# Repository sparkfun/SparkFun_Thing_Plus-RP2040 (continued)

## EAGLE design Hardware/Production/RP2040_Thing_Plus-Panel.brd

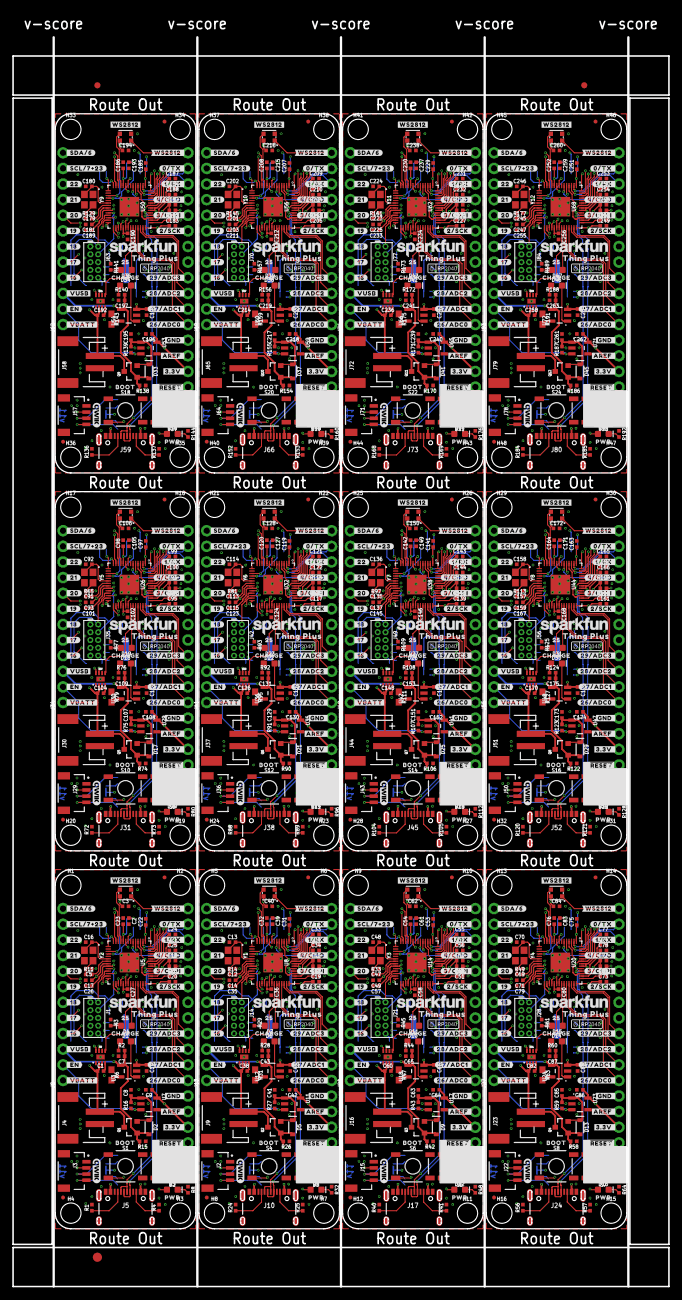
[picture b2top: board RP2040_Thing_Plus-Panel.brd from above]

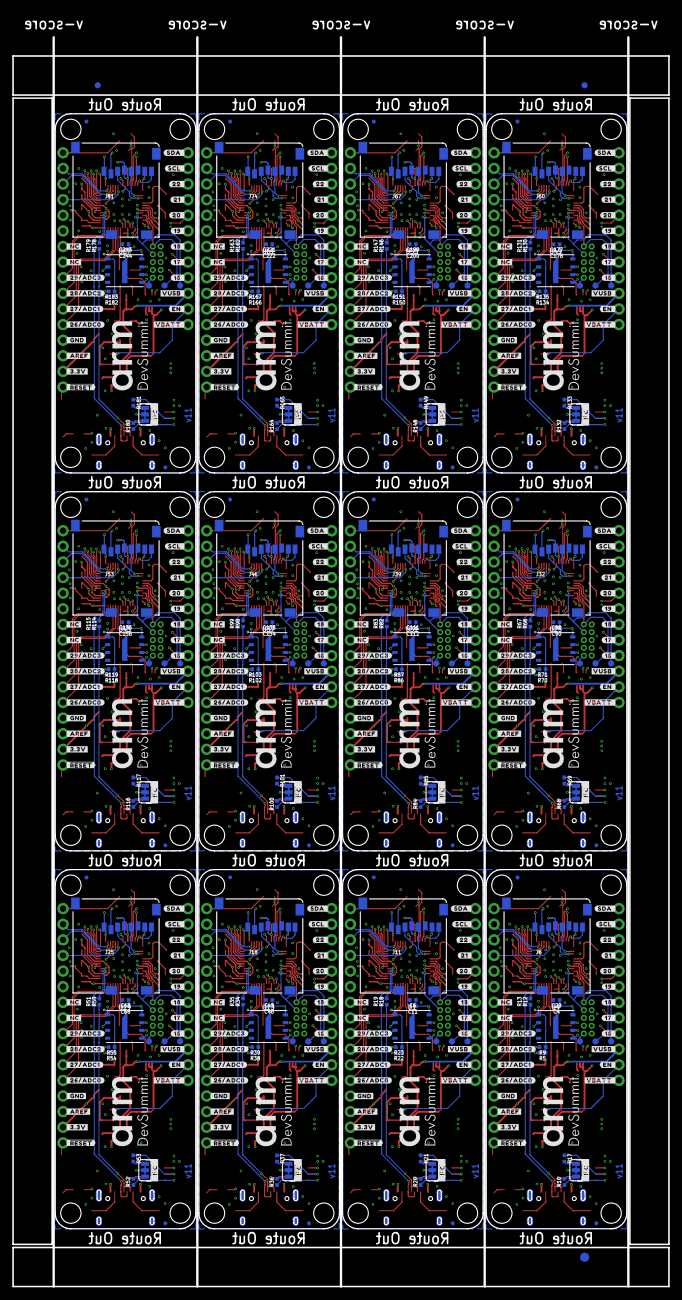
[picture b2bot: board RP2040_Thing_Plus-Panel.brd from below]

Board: 4 copper layers, 106.7 x 203.2 mm, 1566 parts (483 on the bottom side), 744 nets.

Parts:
C1, C2, C3, C6, C14, C15, C17, C18, C19, C20, C21, C22, C23, C24, C25, C29, C30, C31, C32, C33, C34, C38, C39, C40, C45, C49, C50, C51, C52, C53, C54, C55, C56, C60, C61, C62, C67, C71, C72, C73, C74, C75, C76, C77, C78, C82, C83, C84, C89, C93, C94, C95, C96, C97, C98, C99, C100, C104, C105, C106, C111, C115, C116, C117, C118, C119, C120, C121, C122, C126, C127, C128, C133, C137, C138, C139, C140, C141, C142, C143, C144, C148, C149, C150, C155, C159, C160, C161, C162, C163, C164, C165, C166, C170, C171, C172, C177, C181, C182, C183, C184, C185, C186, C187, C188, C192, C193, C194, C199, C203, C204, C205, C206, C207, C208, C209, C210, C214, C215, C216, C221, C225, C226, C227, C228, C229, C230, C231, C232, C236, C237, C238, C243, C247, C248, C249, C250, C251, C252, C253, C254, C258, C259, C260: 0.1uF; 0402-TIGHT
C4, C9, C11, C26, C27, C28, C35, C36, C37, C42, C46, C57, C58, C59, C64, C68, C79, C80, C81, C86, C90, C101, C102, C103, C108, C112, C123, C124, C125, C130, C134, C145, C146, C147, C152, C156, C167, C168, C169, C174, C178, C189, C190, C191, C196, C200, C211, C212, C213, C218, C222, C233, C234, C235, C240, C244, C255, C256, C257, C262: 2.2uF; 0402-TIGHT
C5, C12, C13, C16, C47, C48, C69, C70, C91, C92, C113, C114, C135, C136, C157, C158, C179, C180, C201, C202, C223, C224, C245, C246: 15pF; 0402-TIGHT
C7, C10, C43, C44, C65, C66, C87, C88, C109, C110, C131, C132, C153, C154, C175, C176, C197, C198, C219, C220, C241, C242, C263, C264: 4.7uF; 0402-TIGHT
C8, C41, C63, C85, C107, C129, C151, C173, C195, C217, C239, C261: 1.0uF; 0402-TIGHT
D1, D6, D10, D14, D18, D22, D26, D30, D34, D38, D42, D46: Yellow; LED-0603
D2, D5, D9, D13, D17, D21, D25, D29, D33, D37, D41, D45: 1A/23V/620mV; SOD-323
D3, D8, D12, D16, D20, D24, D28, D32, D36, D40, D44, D48: RED; LED-0603
D4, D7, D11, D15, D19, D23, D27, D31, D35, D39, D43, D47: BLUE; LED-0603
E$1, E$2, E$3, E$4: FIDUCIAL-1X2
E$5, E$6: FIDUCIAL-1.5X3
FD1, FD2, FD3, FD4, FD5, FD6, FD7, FD8, FD9, FD10, FD11, FD12, FD13, FD14, FD15, FD16, FD17, FD18, FD19, FD20, FD21, FD22, FD23, FD24, FD25, FD26, FD27, FD28, FD29, FD30, FD31, FD32, FD33, FD34, FD35, FD36, FD37, FD38, FD39, FD40, FD41, FD42, FD43, FD44, FD45, FD46, FD47, FD48: FIDUCIALUFIDUCIAL; FIDUCIAL-MICRO
H1, H2, H3, H4, H5, H6, H7, H8, H9, H10, H11, H12, H13, H14, H15, H16, H17, H18, H19, H20, H21, H22, H23, H24, H25, H26, H27, H28, H29, H30, H31, H32, H33, H34, H35, H36, H37, H38, H39, H40, H41, H42, H43, H44, H45, H46, H47, H48: STAND-OFF
J1, J14, J21, J28, J35, J42, J49, J56, J63, J70, J77, J84: SWD; 2X5-PTH-1.27MM
J2, J3, J15, J22, J29, J36, J43, J50, J57, J64, J71, J78: Qwiic; JST04_1MM_RA
J4, J9, J16, J23, J30, J37, J44, J51, J58, J65, J72, J79: JST-2-SMD
J5, J10, J17, J24, J31, J38, J45, J52, J59, J66, J73, J80: USB C; USB-C-16P-4LAYER-ISOLATED
J6, J11, J18, J25, J32, J39, J46, J53, J60, J67, J74, J81: microSD; MICRO-SD-SOCKET
J7, J12, J19, J26, J33, J40, J47, J54, J61, J68, J75, J82: 1X16_NO_SILK
J8, J13, J20, J27, J34, J41, J48, J55, J62, J69, J76, J83: 1X12_NO_SILK
JP1, JP2, JP3, JP4, JP5, JP6, JP7, JP8, JP9, JP10, JP11, JP12: JUMPER-SMT_3_2-NC_TRACE_SILK; SMT-JUMPER_3_2-NC_TRACE_SILK
Q1, Q2, Q3, Q4, Q5, Q6, Q7, Q8, Q9, Q10, Q11, Q12: 20V/4.2A/52mΩ/1.4W; SOT23-3
R1, R4, R24, R25, R40, R41, R56, R57, R72, R73, R88, R89, R104, R105, R120, R121, R136, R137, R152, R153, R168, R169, R184, R185: 5.1k; 0402-TIGHT
R2, R3, R5, R8, R11, R14, R22, R28, R29, R32, R33, R38, R44, R45, R48, R49, R54, R60, R61, R64, R65, R70, R76, R77, R80, R81, R86, R92, R93, R96, R97, R102, R108, R109, R112, R113, R118, R124, R125, R128, R129, R134, R140, R141, R144, R145, R150, R156, R157, R160, R161, R166, R172, R173, R176, R177, R182, R188, R189, R192: 1k; 0402-TIGHT
R6, R31, R47, R63, R79, R95, R111, R127, R143, R159, R175, R191: 2.0k; 0603
R7, R30, R46, R62, R78, R94, R110, R126, R142, R158, R174, R190: 200OHM-0402T-1/16W-1%; 0402-TIGHT
R9, R15, R16, R23, R26, R27, R39, R42, R43, R55, R58, R59, R71, R74, R75, R87, R90, R91, R103, R106, R107, R119, R122, R123, R135, R138, R139, R151, R154, R155, R167, R170, R171, R183, R186, R187: 10k; 0402-TIGHT
R10, R17, R20, R21, R36, R37, R52, R53, R68, R69, R84, R85, R100, R101, R116, R117, R132, R133, R148, R149, R164, R165, R180, R181: 2.2k; 0402-TIGHT
R12, R13, R18, R19, R34, R35, R50, R51, R66, R67, R82, R83, R98, R99, R114, R115, R130, R131, R146, R147, R162, R163, R178, R179: 27; 0402-TIGHT
S1, S2, S3, S4, S5, S6, S7, S8, S9, S10, S11, S12, S13, S14, S15, S16, S17, S18, S19, S20, S21, S22, S23, S24: MOMENTARY-SWITCH-SPST-SMD-5.2MM-TALL; TACTILE_SWITCH_SMD_5.2MM
TP1, TP2, TP3, TP4, TP5, TP6, TP7, TP8, TP9, TP10, TP11, TP12, TP13, TP14, TP15, TP16, TP17, TP18, TP19, TP20, TP21, TP22, TP23, TP24, TP25, TP26, TP27, TP28, TP29, TP30, TP31, TP32, TP33, TP34, TP35, TP36: PAD.03X.04
U1, U4, U13, U19, U25, U31, U37, U43, U49, U55, U61, U67: W25QXX128MBIT; WSON-8-6X5-SKINNY_CENTERPAD
U2, U9, U15, U21, U27, U33, U39, U45, U51, U57, U63, U69: MAX17048; DFN-8
U3, U12, U18, U24, U30, U36, U42, U48, U54, U60, U66, U72: MCP73831; SOT23-5
U5, U8, U14, U20, U26, U32, U38, U44, U50, U56, U62, U68: RP2040; QFN-56
U6, U10, U16, U22, U28, U34, U40, U46, U52, U58, U64, U70: WS2812-2020
U7, U11, U17, U23, U29, U35, U41, U47, U53, U59, U65, U71: 3.3V; SOT23-5
U$1, U$31, U$119, U$178, U$237, U$296, U$355, U$414, U$473, U$532, U$591, U$650: #_16#0
U$2, U$32, U$120, U$179, U$238, U$297, U$356, U$415, U$474, U$533, U$592, U$651: #_17#0
U$3, U$43, U$121, U$180, U$239, U$298, U$357, U$416, U$475, U$534, U$593, U$652: #_18#0
U$4, U$44, U$122, U$181, U$240, U$299, U$358, U$417, U$476, U$535, U$594, U$653: #_19#0
U$5, U$46, U$123, U$182, U$241, U$300, U$359, U$418, U$477, U$536, U$595, U$654: #_20#0
U$6, U$48, U$124, U$183, U$242, U$301, U$360, U$419, U$478, U$537, U$596, U$655: #_21#0
U$7, U$49, U$125, U$184, U$243, U$302, U$361, U$420, U$479, U$538, U$597, U$656: #_22#0
U$8, U$73, U$132, U$191, U$250, U$309, U$368, U$427, U$486, U$545, U$604, U$663: #_SCL#7#23#0
U$9, U$74, U$133, U$192, U$251, U$310, U$369, U$428, U$487, U$546, U$605, U$664: #_SDA#6#0
U$10, U$50, U$126, U$185, U$244, U$303, U$362, U$421, U$480, U$539, U$598, U$657: #WS2812_#0
U$11, U$51, U$127, U$186, U$245, U$304, U$363, U$422, U$481, U$540, U$599, U$658: #0#TX_#0
U$12, U$52, U$128, U$187, U$246, U$305, U$364, U$423, U$482, U$541, U$600, U$659: #1#RX_#0
U$13, U$53, U$129, U$188, U$247, U$306, U$365, U$424, U$483, U$542, U$601, U$660: #4#CIPO_#0
U$14, U$71, U$130, U$189, U$248, U$307, U$366, U$425, U$484, U$543, U$602, U$661: #3#COPI_#0
U$15, U$72, U$131, U$190, U$249, U$308, U$367, U$426, U$485, U$544, U$603, U$662: #2#SCK_#0
U$16, U$113, U$172, U$231, U$290, U$349, U$408, U$467, U$526, U$585, U$644, U$703: PWR0
U$17, U$114, U$173, U$232, U$291, U$350, U$409, U$468, U$527, U$586, U$645, U$704: #I�C#0
U$18, U$75, U$134, U$193, U$252, U$311, U$370, U$429, U$488, U$547, U$606, U$665: #29#ADC3_#0
U$19, U$76, U$135, U$194, U$253, U$312, U$371, U$430, U$489, U$548, U$607, U$666: #28#ADC2_#0
U$20, U$77, U$136, U$195, U$254, U$313, U$372, U$431, U$490, U$549, U$608, U$667: #27#ADC1_#0
U$21, U$78, U$137, U$196, U$255, U$314, U$373, U$432, U$491, U$550, U$609, U$668: #26#ADC0_#0
U$22, U$79, U$138, U$197, U$256, U$315, U$374, U$433, U$492, U$551, U$610, U$669: #_VUSB#0
U$23, U$80, U$139, U$198, U$257, U$316, U$375, U$434, U$493, U$552, U$611, U$670: #_EN#0
U$24, U$81, U$140, U$199, U$258, U$317, U$376, U$435, U$494, U$553, U$612, U$671: #_VBATT#0
U$25, U$82, U$141, U$200, U$259, U$318, U$377, U$436, U$495, U$554, U$613, U$672: #GND_#0
U$26, U$83, U$142, U$201, U$260, U$319, U$378, U$437, U$496, U$555, U$614, U$673: #AREF_#0
U$27, U$84, U$143, U$202, U$261, U$320, U$379, U$438, U$497, U$556, U$615, U$674: #3#3V_#0
U$28, U$85, U$144, U$203, U$262, U$321, U$380, U$439, U$498, U$557, U$616, U$675: ##RESET##0
U$29, U$117, U$176, U$235, U$294, U$353, U$412, U$471, U$530, U$589, U$648, U$707: RP2040_10
U$30, U$118, U$177, U$236, U$295, U$354, U$413, U$472, U$531, U$590, U$649, U$708: ARM1848_DEVSUMMIT_2021_LOGOS_ST3_STACKED#BLACK#JPG
U$33, U$101, U$160, U$219, U$278, U$337, U$396, U$455, U$514, U$573, U$632, U$691: #SCL_#0
U$34, U$102, U$161, U$220, U$279, U$338, U$397, U$456, U$515, U$574, U$633, U$692: #SDA_#0
U$35, U$103, U$162, U$221, U$280, U$339, U$398, U$457, U$516, U$575, U$634, U$693: #_#RESET##0
U$36, U$104, U$163, U$222, U$281, U$340, U$399, U$458, U$517, U$576, U$635, U$694: #_3#3V#0
U$37, U$105, U$164, U$223, U$282, U$341, U$400, U$459, U$518, U$577, U$636, U$695: #_AREF#0
U$38, U$106, U$165, U$224, U$283, U$342, U$401, U$460, U$519, U$578, U$637, U$696: #_GND#0
U$39, U$107, U$166, U$225, U$284, U$343, U$402, U$461, U$520, U$579, U$638, U$697: #_26#ADC0#0
U$40, U$108, U$167, U$226, U$285, U$344, U$403, U$462, U$521, U$580, U$639, U$698: #_27#ADC1#0
U$41, U$109, U$168, U$227, U$286, U$345, U$404, U$463, U$522, U$581, U$640, U$699: #_28#ADC2#0
U$42, U$110, U$169, U$228, U$287, U$346, U$405, U$464, U$523, U$582, U$641, U$700: #_29#ADC3#0
U$45, U$115, U$174, U$233, U$292, U$351, U$410, U$469, U$528, U$587, U$646, U$705: SFE_LOGO_NAME_.1
U$47, U$116, U$175, U$234, U$293, U$352, U$411, U$470, U$529, U$588, U$647, U$706: THING_PLUS_0
U$54, U$88, U$147, U$206, U$265, U$324, U$383, U$442, U$501, U$560, U$619, U$678: 250
U$55, U$89, U$148, U$207, U$266, U$325, U$384, U$443, U$502, U$561, U$620, U$679: CHARGE0
U$56, U$90, U$149, U$208, U$267, U$326, U$385, U$444, U$503, U$562, U$621, U$680: BOOT0
U$57, U$91, U$150, U$209, U$268, U$327, U$386, U$445, U$504, U$563, U$622, U$681: #22_#0
U$58, U$92, U$151, U$210, U$269, U$328, U$387, U$446, U$505, U$564, U$623, U$682: #21_#0
U$59, U$93, U$152, U$211, U$270, U$329, U$388, U$447, U$506, U$565, U$624, U$683: #20_#0
U$60, U$86, U$145, U$204, U$263, U$322, U$381, U$440, U$499, U$558, U$617, U$676: #WS2812#0
U$61, U$94, U$153, U$212, U$271, U$330, U$389, U$448, U$507, U$566, U$625, U$684: #19_#0
U$62, U$95, U$154, U$213, U$272, U$331, U$390, U$449, U$508, U$567, U$626, U$685: #18_#0
U$63, U$96, U$155, U$214, U$273, U$332, U$391, U$450, U$509, U$568, U$627, U$686: #17_#0
U$64, U$87, U$146, U$205, U$264, U$323, U$382, U$441, U$500, U$559, U$618, U$677: QWIIC_4MM
U$65, U$97, U$156, U$215, U$274, U$333, U$392, U$451, U$510, U$569, U$628, U$687: #16_#0
U$66, U$98, U$157, U$216, U$275, U$334, U$393, U$452, U$511, U$570, U$629, U$688: #VUSB_#0
U$67, U$99, U$158, U$217, U$276, U$335, U$394, U$453, U$512, U$571, U$630, U$689: #EN_#0
U$68, U$100, U$159, U$218, U$277, U$336, U$395, U$454, U$513, U$572, U$631, U$690: #VBATT_#0
U$69, U$70, U$111, U$112, U$170, U$171, U$229, U$230, U$288, U$289, U$347, U$348, U$406, U$407, U$465, U$466, U$524, U$525, U$583, U$584, U$642, U$643, U$701, U$702: #_NC#0
Y1, Y2, Y3, Y4, Y5, Y6, Y7, Y8, Y9, Y10, Y11, Y12: 12MHz; CRYSTAL-SMD-2X2.5MM

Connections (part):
1.1V: C24.1, C25.1, C26.1, U5.23, U5.45, U5.50
1.1V1: C33.1, C34.1, C35.1, U8.23, U8.45, U8.50
1.1V2: C55.1, C56.1, C57.1, U14.23, U14.45, U14.50
1.1V3: C77.1, C78.1, C79.1, U20.23, U20.45, U20.50
1.1V4: C99.1, C100.1, C101.1, U26.23, U26.45, U26.50
1.1V5: C121.1, C122.1, C123.1, U32.23, U32.45, U32.50
1.1V6: C143.1, C144.1, C145.1, U38.23, U38.45, U38.50
1.1V7: C165.1, C166.1, C167.1, U44.23, U44.45, U44.50
1.1V8: C187.1, C188.1, C189.1, U50.23, U50.45, U50.50
1.1V9: C209.1, C210.1, C211.1, U56.23, U56.45, U56.50
1.1V10: C231.1, C232.1, C233.1, U62.23, U62.45, U62.50
1.1V11: C253.1, C254.1, C255.1, U68.23, U68.45, U68.50
3.3V: C2.1, C3.1, C4.1, C9.1, C17.1, C18.1, C20.1, C21.1, C22.1, C23.1, C27.1, C29.1, D3.A, J1.1, J3.2, J6.VCC, J7.2, JP1.2, R7.2, R9.2, U4.8, U5.1, U5.10, U5.22, U5.33, U5.42, U5.44, U5.48, U5.49, U6.4, U7.5
3.3V1: C6.1, C11.1, C14.1, C15.1, C19.1, C30.1, C31.1, C32.1, C36.1, C39.1, C40.1, C42.1, D8.A, J2.2, J11.VCC, J12.2, J14.1, JP2.2, R23.2, R30.2, U1.8, U8.1, U8.10, U8.22, U8.33, U8.42, U8.44, U8.48, U8.49, U10.4, U11.5
3.3V2: C45.1, C46.1, C49.1, C50.1, C51.1, C52.1, C53.1, C54.1, C58.1, C61.1, C62.1, C64.1, D12.A, J15.2, J18.VCC, J19.2, J21.1, JP3.2, R39.2, R46.2, U13.8, U14.1, U14.10, U14.22, U14.33, U14.42, U14.44, U14.48, U14.49, U16.4, U17.5
3.3V3: C67.1, C68.1, C71.1, C72.1, C73.1, C74.1, C75.1, C76.1, C80.1, C83.1, C84.1, C86.1, D16.A, J22.2, J25.VCC, J26.2, J28.1, JP4.2, R55.2, R62.2, U19.8, U20.1, U20.10, U20.22, U20.33, U20.42, U20.44, U20.48, U20.49, U22.4, U23.5
3.3V4: C89.1, C90.1, C93.1, C94.1, C95.1, C96.1, C97.1, C98.1, C102.1, C105.1, C106.1, C108.1, D20.A, J29.2, J32.VCC, J33.2, J35.1, JP5.2, R71.2, R78.2, U25.8, U26.1, U26.10, U26.22, U26.33, U26.42, U26.44, U26.48, U26.49, U28.4, U29.5
3.3V5: C111.1, C112.1, C115.1, C116.1, C117.1, C118.1, C119.1, C120.1, C124.1, C127.1, C128.1, C130.1, D24.A, J36.2, J39.VCC, J40.2, J42.1, JP6.2, R87.2, R94.2, U31.8, U32.1, U32.10, U32.22, U32.33, U32.42, U32.44, U32.48, U32.49, U34.4, U35.5
3.3V6: C133.1, C134.1, C137.1, C138.1, C139.1, C140.1, C141.1, C142.1, C146.1, C149.1, C150.1, C152.1, D28.A, J43.2, J46.VCC, J47.2, J49.1, JP7.2, R103.2, R110.2, U37.8, U38.1, U38.10, U38.22, U38.33, U38.42, U38.44, U38.48, U38.49, U40.4, U41.5
3.3V7: C155.1, C156.1, C159.1, C160.1, C161.1, C162.1, C163.1, C164.1, C168.1, C171.1, C172.1, C174.1, D32.A, J50.2, J53.VCC, J54.2, J56.1, JP8.2, R119.2, R126.2, U43.8, U44.1, U44.10, U44.22, U44.33, U44.42, U44.44, U44.48, U44.49, U46.4, U47.5
3.3V8: C177.1, C178.1, C181.1, C182.1, C183.1, C184.1, C185.1, C186.1, C190.1, C193.1, C194.1, C196.1, D36.A, J57.2, J60.VCC, J61.2, J63.1, JP9.2, R135.2, R142.2, U49.8, U50.1, U50.10, U50.22, U50.33, U50.42, U50.44, U50.48, U50.49, U52.4, U53.5
3.3V9: C199.1, C200.1, C203.1, C204.1, C205.1, C206.1, C207.1, C208.1, C212.1, C215.1, C216.1, C218.1, D40.A, J64.2, J67.VCC, J68.2, J70.1, JP10.2, R151.2, R158.2, U55.8, U56.1, U56.10, U56.22, U56.33, U56.42, U56.44, U56.48, U56.49, U58.4, U59.5
3.3V10: C221.1, C222.1, C225.1, C226.1, C227.1, C228.1, C229.1, C230.1, C234.1, C237.1, C238.1, C240.1, D44.A, J71.2, J74.VCC, J75.2, J77.1, JP11.2, R167.2, R174.2, U61.8, U62.1, U62.10, U62.22, U62.33, U62.42, U62.44, U62.48, U62.49, U64.4, U65.5
3.3V11: C243.1, C244.1, C247.1, C248.1, C249.1, C250.1, C251.1, C252.1, C256.1, C259.1, C260.1, C262.1, D48.A, J78.2, J81.VCC, J82.2, J84.1, JP12.2, R183.2, R190.2, U67.8, U68.1, U68.10, U68.22, U68.33, U68.42, U68.44, U68.48, U68.49, U70.4, U71.5
!RESET!: J1.10, J7.1, S2.3, TP3.P$1, U5.26
!RESET!1: J12.1, J14.10, S3.3, TP6.P$1, U8.26
!RESET!2: J19.1, J21.10, S5.3, TP9.P$1, U14.26
!RESET!3: J26.1, J28.10, S7.3, TP12.P$1, U20.26
!RESET!4: J33.1, J35.10, S9.3, TP15.P$1, U26.26
!RESET!5: J40.1, J42.10, S11.3, TP18.P$1, U32.26
!RESET!6: J47.1, J49.10, S13.3, TP21.P$1, U38.26
!RESET!7: J54.1, J56.10, S15.3, TP24.P$1, U44.26
!RESET!8: J61.1, J63.10, S17.3, TP27.P$1, U50.26
!RESET!9: J68.1, J70.10, S19.3, TP30.P$1, U56.26
!RESET!10: J75.1, J77.10, S21.3, TP33.P$1, U62.26
!RESET!11: J82.1, J84.10, S23.3, TP36.P$1, U68.26
ADC0: J7.5, U5.38
ADC1: J7.6, U5.39
ADC2: J7.7, U5.40
ADC3: J7.8, U5.41
ADC4: J12.8, U8.41
ADC5: J12.5, U8.38
ADC6: J12.6, U8.39
ADC7: J12.7, U8.40
ADC8: J19.8, U14.41
ADC9: J19.5, U14.38
ADC10: J19.6, U14.39
ADC11: J19.7, U14.40
ADC12: J26.8, U20.41
ADC13: J26.5, U20.38
ADC14: J26.6, U20.39
ADC15: J26.7, U20.40
ADC16: J33.8, U26.41
ADC17: J33.5, U26.38
ADC18: J33.6, U26.39
ADC19: J33.7, U26.40
ADC20: J40.8, U32.41
ADC21: J40.5, U32.38
ADC22: J40.6, U32.39
ADC23: J40.7, U32.40
ADC24: J47.8, U38.41
ADC25: J47.5, U38.38
ADC26: J47.6, U38.39
ADC27: J47.7, U38.40
ADC28: J54.8, U44.41
ADC29: J54.5, U44.38
ADC30: J54.6, U44.39
ADC31: J54.7, U44.40
ADC32: J61.8, U50.41
ADC33: J61.5, U50.38
ADC34: J61.6, U50.39
ADC35: J61.7, U50.40
ADC36: J68.8, U56.41
ADC37: J68.5, U56.38
ADC38: J68.6, U56.39
ADC39: J68.7, U56.40
ADC40: J75.8, U62.41
ADC41: J75.5, U62.38
ADC42: J75.6, U62.39
ADC43: J75.7, U62.40
ADC44: J82.8, U68.41
ADC45: J82.5, U68.38
ADC46: J82.6, U68.39
ADC47: J82.7, U68.40
AVDD: C28.1, J7.3, R7.1, U5.43
AVDD1: C37.1, J12.3, R30.1, U8.43
AVDD2: C59.1, J19.3, R46.1, U14.43
AVDD3: C81.1, J26.3, R62.1, U20.43
AVDD4: C103.1, J33.3, R78.1, U26.43
AVDD5: C125.1, J40.3, R94.1, U32.43
AVDD6: C147.1, J47.3, R110.1, U38.43
AVDD7: C169.1, J54.3, R126.1, U44.43
AVDD8: C191.1, J61.3, R142.1, U50.43
AVDD9: C213.1, J68.3, R158.1, U56.43
AVDD10: C235.1, J75.3, R174.1, U62.43
AVDD11: C257.1, J82.3, R190.1, U68.43
BATT_ALERT: U2.5, U5.36
BATT_ALERT1: U8.36, U9.5
BATT_ALERT2: U14.36, U15.5
BATT_ALERT3: U20.36, U21.5
BATT_ALERT4: U26.36, U27.5
BATT_ALERT5: U32.36, U33.5
BATT_ALERT6: U38.36, U39.5
BATT_ALERT7: U44.36, U45.5
BATT_ALERT8: U50.36, U51.5
BATT_ALERT9: U56.36, U57.5
BATT_ALERT10: U62.36, U63.5
BATT_ALERT11: U68.36, U69.5
BOOT: R5.2, S1.3
BOOT1: R22.2, S4.3
BOOT2: R38.2, S6.3
BOOT3: R54.2, S8.3
BOOT4: R70.2, S10.3
BOOT5: R86.2, S12.3
BOOT6: R102.2, S14.3
BOOT7: R118.2, S16.3
BOOT8: R134.2, S18.3
BOOT9: R150.2, S20.3
BOOT10: R166.2, S22.3
BOOT11: R182.2, S24.3
EN: J8.2, R16.1, U7.3
EN1: J13.2, R27.1, U11.3
EN2: J20.2, R43.1, U17.3
EN3: J27.2, R59.1, U23.3
EN4: J34.2, R75.1, U29.3
EN5: J41.2, R91.1, U35.3
EN6: J48.2, R107.1, U41.3
EN7: J55.2, R123.1, U47.3
EN8: J62.2, R139.1, U53.3
EN9: J69.2, R155.1, U59.3
EN10: J76.2, R171.1, U65.3
EN11: J83.2, R187.1, U71.3
GND: C1.2, C2.2, C3.2, C4.2, C5.1, C7.2, C8.2, C9.2, C10.2, C16.1, C17.2, C18.2, C20.2, C21.2, C22.2, C23.2, C24.2, C25.2, C26.2, C27.2, C28.2, C29.2, J1.3, J1.5, J1.9, J3.1, J4.1, J5.GND, J5.GND2, J6.CD1, J6.GND, J6.GND1, J6.GND3, J7.4, R1.2, R3.1, R4.2, R6.1, R8.1, R15.1, S1.1, S2.1, U2.1, U2.4, U2.6, U2.9, U3.2, U4.4, U5.19, U5.EPAD, U6.2, U7.2
GND1: C6.2, C11.2, C12.1, C13.1, C14.2, C15.2, C19.2, C30.2, C31.2, C32.2, C33.2, C34.2, C35.2, C36.2, C37.2, C38.2, C39.2, C40.2, C41.2, C42.2, C43.2, C44.2, J2.1, J9.1, J10.GND, J10.GND2, J11.CD1, J11.GND, J11.GND1, J11.GND3, J12.4, J14.3, J14.5, J14.9, R24.2, R25.2, R26.1, R29.1, R31.1, R32.1, S3.1, S4.1, U1.4, U8.19, U8.EPAD, U9.1, U9.4, U9.6, U9.9, U10.2, U11.2, U12.2
GND2: C45.2, C46.2, C47.1, C48.1, C49.2, C50.2, C51.2, C52.2, C53.2, C54.2, C55.2, C56.2, C57.2, C58.2, C59.2, C60.2, C61.2, C62.2, C63.2, C64.2, C65.2, C66.2, J15.1, J16.1, J17.GND, J17.GND2, J18.CD1, J18.GND, J18.GND1, J18.GND3, J19.4, J21.3, J21.5, J21.9, R40.2, R41.2, R42.1, R45.1, R47.1, R48.1, S5.1, S6.1, U13.4, U14.19, U14.EPAD, U15.1, U15.4, U15.6, U15.9, U16.2, U17.2, U18.2
GND3: C67.2, C68.2, C69.1, C70.1, C71.2, C72.2, C73.2, C74.2, C75.2, C76.2, C77.2, C78.2, C79.2, C80.2, C81.2, C82.2, C83.2, C84.2, C85.2, C86.2, C87.2, C88.2, J22.1, J23.1, J24.GND, J24.GND2, J25.CD1, J25.GND, J25.GND1, J25.GND3, J26.4, J28.3, J28.5, J28.9, R56.2, R57.2, R58.1, R61.1, R63.1, R64.1, S7.1, S8.1, U19.4, U20.19, U20.EPAD, U21.1, U21.4, U21.6, U21.9, U22.2, U23.2, U24.2
GND4: C89.2, C90.2, C91.1, C92.1, C93.2, C94.2, C95.2, C96.2, C97.2, C98.2, C99.2, C100.2, C101.2, C102.2, C103.2, C104.2, C105.2, C106.2, C107.2, C108.2, C109.2, C110.2, J29.1, J30.1, J31.GND, J31.GND2, J32.CD1, J32.GND, J32.GND1, J32.GND3, J33.4, J35.3, J35.5, J35.9, R72.2, R73.2, R74.1, R77.1, R79.1, R80.1, S9.1, S10.1, U25.4, U26.19, U26.EPAD, U27.1, U27.4, U27.6, U27.9, U28.2, U29.2, U30.2
GND5: C111.2, C112.2, C113.1, C114.1, C115.2, C116.2, C117.2, C118.2, C119.2, C120.2, C121.2, C122.2, C123.2, C124.2, C125.2, C126.2, C127.2, C128.2, C129.2, C130.2, C131.2, C132.2, J36.1, J37.1, J38.GND, J38.GND2, J39.CD1, J39.GND, J39.GND1, J39.GND3, J40.4, J42.3, J42.5, J42.9, R88.2, R89.2, R90.1, R93.1, R95.1, R96.1, S11.1, S12.1, U31.4, U32.19, U32.EPAD, U33.1, U33.4, U33.6, U33.9, U34.2, U35.2, U36.2
GND6: C133.2, C134.2, C135.1, C136.1, C137.2, C138.2, C139.2, C140.2, C141.2, C142.2, C143.2, C144.2, C145.2, C146.2, C147.2, C148.2, C149.2, C150.2, C151.2, C152.2, C153.2, C154.2, J43.1, J44.1, J45.GND, J45.GND2, J46.CD1, J46.GND, J46.GND1, J46.GND3, J47.4, J49.3, J49.5, J49.9, R104.2, R105.2, R106.1, R109.1, R111.1, R112.1, S13.1, S14.1, U37.4, U38.19, U38.EPAD, U39.1, U39.4, U39.6, U39.9, U40.2, U41.2, U42.2
GND7: C155.2, C156.2, C157.1, C158.1, C159.2, C160.2, C161.2, C162.2, C163.2, C164.2, C165.2, C166.2, C167.2, C168.2, C169.2, C170.2, C171.2, C172.2, C173.2, C174.2, C175.2, C176.2, J50.1, J51.1, J52.GND, J52.GND2, J53.CD1, J53.GND, J53.GND1, J53.GND3, J54.4, J56.3, J56.5, J56.9, R120.2, R121.2, R122.1, R125.1, R127.1, R128.1, S15.1, S16.1, U43.4, U44.19, U44.EPAD, U45.1, U45.4, U45.6, U45.9, U46.2, U47.2, U48.2
GND8: C177.2, C178.2, C179.1, C180.1, C181.2, C182.2, C183.2, C184.2, C185.2, C186.2, C187.2, C188.2, C189.2, C190.2, C191.2, C192.2, C193.2, C194.2, C195.2, C196.2, C197.2, C198.2, J57.1, J58.1, J59.GND, J59.GND2, J60.CD1, J60.GND, J60.GND1, J60.GND3, J61.4, J63.3, J63.5, J63.9, R136.2, R137.2, R138.1, R141.1, R143.1, R144.1, S17.1, S18.1, U49.4, U50.19, U50.EPAD, U51.1, U51.4, U51.6, U51.9, U52.2, U53.2, U54.2
GND9: C199.2, C200.2, C201.1, C202.1, C203.2, C204.2, C205.2, C206.2, C207.2, C208.2, C209.2, C210.2, C211.2, C212.2, C213.2, C214.2, C215.2, C216.2, C217.2, C218.2, C219.2, C220.2, J64.1, J65.1, J66.GND, J66.GND2, J67.CD1, J67.GND, J67.GND1, J67.GND3, J68.4, J70.3, J70.5, J70.9, R152.2, R153.2, R154.1, R157.1, R159.1, R160.1, S19.1, S20.1, U55.4, U56.19, U56.EPAD, U57.1, U57.4, U57.6, U57.9, U58.2, U59.2, U60.2
GND10: C221.2, C222.2, C223.1, C224.1, C225.2, C226.2, C227.2, C228.2, C229.2, C230.2, C231.2, C232.2, C233.2, C234.2, C235.2, C236.2, C237.2, C238.2, C239.2, C240.2, C241.2, C242.2, J71.1, J72.1, J73.GND, J73.GND2, J74.CD1, J74.GND, J74.GND1, J74.GND3, J75.4, J77.3, J77.5, J77.9, R168.2, R169.2, R170.1, R173.1, R175.1, R176.1, S21.1, S22.1, U61.4, U62.19, U62.EPAD, U63.1, U63.4, U63.6, U63.9, U64.2, U65.2, U66.2
GND11: C243.2, C244.2, C245.1, C246.1, C247.2, C248.2, C249.2, C250.2, C251.2, C252.2, C253.2, C254.2, C255.2, C256.2, C257.2, C258.2, C259.2, C260.2, C261.2, C262.2, C263.2, C264.2, J78.1, J79.1, J80.GND, J80.GND2, J81.CD1, J81.GND, J81.GND1, J81.GND3, J82.4, J84.3, J84.5, J84.9, R184.2, R185.2, R186.1, R189.1, R191.1, R192.1, S23.1, S24.1, U67.4, U68.19, U68.EPAD, U69.1, U69.4, U69.6, U69.9, U70.2, U71.2, U72.2
GPIO1: J13.4, U8.27
GPIO2: J13.5, U8.28
GPIO3: J13.6, U8.29
GPIO4: J13.7, U8.30
GPIO5: J13.8, U8.31
GPIO6: J13.9, U8.32
GPIO7: J13.10, U8.34
GPIO8: J20.4, U14.27
GPIO9: J20.5, U14.28
GPIO10: J20.6, U14.29
GPIO11: J20.7, U14.30
GPIO12: J20.8, U14.31
GPIO13: J20.9, U14.32
GPIO14: J20.10, U14.34
GPIO15: J27.4, U20.27
GPIO16: J8.4, U5.27
GPIO17: J8.5, U5.28
GPIO18: J8.6, U5.29
GPIO19: J8.7, U5.30
GPIO20: J8.8, U5.31
GPIO21: J8.9, U5.32
GPIO22: J8.10, U5.34
GPIO23: J27.5, U20.28
GPIO24: J27.6, U20.29
GPIO25: J27.7, U20.30
GPIO26: J27.8, U20.31
GPIO27: J27.9, U20.32
GPIO28: J27.10, U20.34
GPIO29: J34.4, U26.27
GPIO30: J34.5, U26.28
GPIO31: J34.6, U26.29
GPIO32: J34.7, U26.30
GPIO33: J34.8, U26.31
GPIO34: J34.9, U26.32
GPIO35: J34.10, U26.34
GPIO36: J41.4, U32.27
GPIO37: J41.5, U32.28
GPIO38: J41.6, U32.29
GPIO39: J41.7, U32.30
GPIO40: J41.8, U32.31
GPIO41: J41.9, U32.32
GPIO42: J41.10, U32.34
GPIO43: J48.4, U38.27
GPIO44: J48.5, U38.28
GPIO45: J48.6, U38.29
GPIO46: J48.7, U38.30
GPIO47: J48.8, U38.31
GPIO48: J48.9, U38.32
GPIO49: J48.10, U38.34
GPIO50: J55.4, U44.27
GPIO51: J55.5, U44.28
GPIO52: J55.6, U44.29
GPIO53: J55.7, U44.30
GPIO54: J55.8, U44.31
GPIO55: J55.9, U44.32
GPIO56: J55.10, U44.34
GPIO57: J62.4, U50.27
GPIO58: J62.5, U50.28
GPIO59: J62.6, U50.29
GPIO60: J62.7, U50.30
GPIO61: J62.8, U50.31
GPIO62: J62.9, U50.32
GPIO63: J62.10, U50.34
GPIO64: J69.4, U56.27
GPIO65: J69.5, U56.28
GPIO66: J69.6, U56.29
GPIO67: J69.7, U56.30
GPIO68: J69.8, U56.31
GPIO69: J69.9, U56.32
GPIO70: J69.10, U56.34
GPIO71: J76.4, U62.27
GPIO72: J76.5, U62.28
GPIO73: J76.6, U62.29
GPIO74: J76.7, U62.30
GPIO75: J76.8, U62.31
GPIO76: J76.9, U62.32
GPIO77: J76.10, U62.34
GPIO78: J83.4, U68.27
GPIO79: J83.5, U68.28
GPIO80: J83.6, U68.29
GPIO81: J83.7, U68.30
GPIO82: J83.8, U68.31
GPIO83: J83.9, U68.32
GPIO84: J83.10, U68.34
I2C1_SCL/GPIO1: J2.4, J13.11, R20.1, U8.9, U8.35, U9.7
I2C1_SCL/GPIO2: J15.4, J20.11, R36.1, U14.9, U14.35, U15.7
I2C1_SCL/GPIO3: J22.4, J27.11, R52.1, U20.9, U20.35, U21.7
I2C1_SCL/GPIO4: J29.4, J34.11, R68.1, U26.9, U26.35, U27.7
I2C1_SCL/GPIO5: J36.4, J41.11, R84.1, U32.9, U32.35, U33.7
I2C1_SCL/GPIO6: J43.4, J48.11, R100.1, U38.9, U38.35, U39.7
I2C1_SCL/GPIO7: J50.4, J55.11, R116.1, U44.9, U44.35, U45.7
I2C1_SCL/GPIO8: J57.4, J62.11, R132.1, U50.9, U50.35, U51.7
I2C1_SCL/GPIO9: J64.4, J69.11, R148.1, U56.9, U56.35, U57.7
I2C1_SCL/GPIO10: J71.4, J76.11, R164.1, U62.9, U62.35, U63.7
I2C1_SCL/GPIO11: J78.4, J83.11, R180.1, U68.9, U68.35, U69.7
I2C1_SCL/GPIO23: J3.4, J8.11, R10.1, U2.7, U5.9, U5.35
I2C1_SDA: J3.3, J8.12, R17.1, U2.8, U5.8
I2C1_SDA1: J2.3, J13.12, R21.1, U8.8, U9.8
I2C1_SDA2: J15.3, J20.12, R37.1, U14.8, U15.8
I2C1_SDA3: J22.3, J27.12, R53.1, U20.8, U21.8
I2C1_SDA4: J29.3, J34.12, R69.1, U26.8, U27.8
I2C1_SDA5: J36.3, J41.12, R85.1, U32.8, U33.8
I2C1_SDA6: J43.3, J48.12, R101.1, U38.8, U39.8
I2C1_SDA7: J50.3, J55.12, R117.1, U44.8, U45.8
I2C1_SDA8: J57.3, J62.12, R133.1, U50.8, U51.8
I2C1_SDA9: J64.3, J69.12, R149.1, U56.8, U57.8
I2C1_SDA10: J71.3, J76.12, R165.1, U62.8, U63.8
I2C1_SDA11: J78.3, J83.12, R181.1, U68.8, U69.8
LED_BUILTIN: D4.A, U5.37
LED_BUILTIN1: D7.A, U8.37
LED_BUILTIN2: D11.A, U14.37
LED_BUILTIN3: D15.A, U20.37
LED_BUILTIN4: D19.A, U26.37
LED_BUILTIN5: D23.A, U32.37
LED_BUILTIN6: D27.A, U38.37
LED_BUILTIN7: D31.A, U44.37
LED_BUILTIN8: D35.A, U50.37
LED_BUILTIN9: D39.A, U56.37
LED_BUILTIN10: D43.A, U62.37
LED_BUILTIN11: D47.A, U68.37
unnamed: D4.C, R3.2
unnamed: JP1.3, R10.2
unnamed: JP1.1, R17.2
unnamed: R11.2, U5.21
unnamed: C16.2, U5.20, Y2.P3
unnamed: C5.2, R11.1, Y2.P1
unnamed: D3.C, R8.2
unnamed: D6.C, U12.1
unnamed: D1.C, U3.1
unnamed: R31.2, U12.5
unnamed: J5.A5, R1.1
unnamed: J5.B5, R4.1
unnamed: D6.A, R28.1
unnamed: R6.2, U3.5
unnamed: C8.1, D2.C, Q1.2, R16.2, U7.1
unnamed: D7.C, R29.2
unnamed: D1.A, R2.1
unnamed: JP2.3, R20.2
unnamed: JP2.1, R21.2
unnamed: R14.2, U8.21
unnamed: C13.2, U8.20, Y1.P3
unnamed: C12.2, R14.1, Y1.P1
unnamed: J10.A5, R24.1
unnamed: J10.B5, R25.1
unnamed: C41.1, D5.C, Q2.2, R27.2, U11.1
unnamed: D8.C, R32.2
unnamed: D10.C, U18.1
unnamed: R47.2, U18.5
unnamed: D10.A, R44.1
unnamed: D11.C, R45.2
unnamed: JP3.3, R36.2
unnamed: JP3.1, R37.2
unnamed: R33.2, U14.21
unnamed: C48.2, U14.20, Y3.P3
unnamed: C47.2, R33.1, Y3.P1
unnamed: J17.A5, R40.1
unnamed: J17.B5, R41.1
unnamed: C63.1, D9.C, Q3.2, R43.2, U17.1
unnamed: D12.C, R48.2
unnamed: D14.C, U24.1
unnamed: R63.2, U24.5
unnamed: D14.A, R60.1
unnamed: D15.C, R61.2
unnamed: JP4.3, R52.2
unnamed: JP4.1, R53.2
unnamed: R49.2, U20.21
unnamed: C70.2, U20.20, Y4.P3
unnamed: C69.2, R49.1, Y4.P1
unnamed: J24.A5, R56.1
unnamed: J24.B5, R57.1
unnamed: C85.1, D13.C, Q4.2, R59.2, U23.1
unnamed: D16.C, R64.2
unnamed: D18.C, U30.1
unnamed: R79.2, U30.5
unnamed: D18.A, R76.1
unnamed: D19.C, R77.2
unnamed: JP5.3, R68.2
unnamed: JP5.1, R69.2
unnamed: R65.2, U26.21
unnamed: C92.2, U26.20, Y5.P3
unnamed: C91.2, R65.1, Y5.P1
unnamed: J31.A5, R72.1
unnamed: J31.B5, R73.1
unnamed: C107.1, D17.C, Q5.2, R75.2, U29.1
unnamed: D20.C, R80.2
unnamed: D22.C, U36.1
unnamed: R95.2, U36.5
unnamed: D22.A, R92.1
unnamed: D23.C, R93.2
unnamed: JP6.3, R84.2
unnamed: JP6.1, R85.2
unnamed: R81.2, U32.21
unnamed: C114.2, U32.20, Y6.P3
unnamed: C113.2, R81.1, Y6.P1
unnamed: J38.A5, R88.1
unnamed: J38.B5, R89.1
unnamed: C129.1, D21.C, Q6.2, R91.2, U35.1
unnamed: D24.C, R96.2
unnamed: D26.C, U42.1
unnamed: R111.2, U42.5
unnamed: D26.A, R108.1
unnamed: D27.C, R109.2
unnamed: JP7.3, R100.2
unnamed: JP7.1, R101.2
unnamed: R97.2, U38.21
unnamed: C136.2, U38.20, Y7.P3
unnamed: C135.2, R97.1, Y7.P1
unnamed: J45.A5, R104.1
unnamed: J45.B5, R105.1
unnamed: C151.1, D25.C, Q7.2, R107.2, U41.1
unnamed: D28.C, R112.2
unnamed: D30.C, U48.1
unnamed: R127.2, U48.5
unnamed: D30.A, R124.1
unnamed: D31.C, R125.2
unnamed: JP8.3, R116.2
unnamed: JP8.1, R117.2
unnamed: R113.2, U44.21
unnamed: C158.2, U44.20, Y8.P3
unnamed: C157.2, R113.1, Y8.P1
unnamed: J52.A5, R120.1
unnamed: J52.B5, R121.1
unnamed: C173.1, D29.C, Q8.2, R123.2, U47.1
unnamed: D32.C, R128.2
unnamed: D34.C, U54.1
unnamed: R143.2, U54.5
unnamed: D34.A, R140.1
unnamed: D35.C, R141.2
unnamed: JP9.3, R132.2
unnamed: JP9.1, R133.2
unnamed: R129.2, U50.21
unnamed: C180.2, U50.20, Y9.P3
unnamed: C179.2, R129.1, Y9.P1
unnamed: J59.A5, R136.1
unnamed: J59.B5, R137.1
unnamed: C195.1, D33.C, Q9.2, R139.2, U53.1
unnamed: D36.C, R144.2
unnamed: D38.C, U60.1
unnamed: R159.2, U60.5
unnamed: D38.A, R156.1
unnamed: D39.C, R157.2
unnamed: JP10.3, R148.2
unnamed: JP10.1, R149.2
unnamed: R145.2, U56.21
unnamed: C202.2, U56.20, Y10.P3
unnamed: C201.2, R145.1, Y10.P1
unnamed: J66.A5, R152.1
unnamed: J66.B5, R153.1
unnamed: C217.1, D37.C, Q10.2, R155.2, U59.1
unnamed: D40.C, R160.2
unnamed: D42.C, U66.1
unnamed: R175.2, U66.5
unnamed: D42.A, R172.1
unnamed: D43.C, R173.2
unnamed: JP11.3, R164.2
unnamed: JP11.1, R165.2
unnamed: R161.2, U62.21
unnamed: C224.2, U62.20, Y11.P3
unnamed: C223.2, R161.1, Y11.P1
unnamed: J73.A5, R168.1
unnamed: J73.B5, R169.1
unnamed: C239.1, D41.C, Q11.2, R171.2, U65.1
unnamed: D44.C, R176.2
unnamed: D46.C, U72.1
unnamed: R191.2, U72.5
unnamed: D46.A, R188.1
unnamed: D47.C, R189.2
unnamed: JP12.3, R180.2
unnamed: JP12.1, R181.2
unnamed: R177.2, U68.21
unnamed: C246.2, U68.20, Y12.P3
unnamed: C245.2, R177.1, Y12.P1
unnamed: J80.A5, R184.1
unnamed: J80.B5, R185.1
unnamed: C261.1, D45.C, Q12.2, R187.2, U71.1
unnamed: D48.C, R192.2
QSPI-0: U4.5, U5.53
QSPI-1: U4.2, U5.55
QSPI-2: U4.3, U5.54
QSPI-3: U4.7, U5.51
QSPI-4: U1.5, U8.53
QSPI-5: U1.7, U8.51
QSPI-6: U1.2, U8.55
QSPI-7: U1.3, U8.54
QSPI-8: U13.5, U14.53
QSPI-9: U13.7, U14.51
QSPI-10: U13.2, U14.55
QSPI-11: U13.3, U14.54
QSPI-12: U19.5, U20.53
QSPI-13: U19.7, U20.51
QSPI-14: U19.2, U20.55
QSPI-15: U19.3, U20.54
QSPI-16: U25.5, U26.53
QSPI-17: U25.7, U26.51
QSPI-18: U25.2, U26.55
QSPI-19: U25.3, U26.54
QSPI-20: U31.5, U32.53
QSPI-21: U31.7, U32.51
QSPI-22: U31.2, U32.55
QSPI-23: U31.3, U32.54
QSPI-24: U37.5, U38.53
QSPI-25: U37.7, U38.51
QSPI-26: U37.2, U38.55
QSPI-27: U37.3, U38.54
QSPI-28: U43.5, U44.53
QSPI-29: U43.7, U44.51
QSPI-30: U43.2, U44.55
QSPI-31: U43.3, U44.54
QSPI-32: U49.5, U50.53
QSPI-33: U49.7, U50.51
QSPI-34: U49.2, U50.55
QSPI-35: U49.3, U50.54
QSPI-36: U55.5, U56.53
QSPI-37: U55.7, U56.51
QSPI-38: U55.2, U56.55
QSPI-39: U55.3, U56.54
QSPI-40: U61.5, U62.53
QSPI-41: U61.7, U62.51
QSPI-42: U61.2, U62.55
QSPI-43: U61.3, U62.54
QSPI-44: U67.5, U68.53
QSPI-45: U67.7, U68.51
QSPI-46: U67.2, U68.55
QSPI-47: U67.3, U68.54
QSPI-CLK: U4.6, U5.52
QSPI-CLK1: U1.6, U8.52
QSPI-CLK2: U13.6, U14.52
QSPI-CLK3: U19.6, U20.52
QSPI-CLK4: U25.6, U26.52
QSPI-CLK5: U31.6, U32.52
QSPI-CLK6: U37.6, U38.52
QSPI-CLK7: U43.6, U44.52
QSPI-CLK8: U49.6, U50.52
QSPI-CLK9: U55.6, U56.52
QSPI-CLK10: U61.6, U62.52
QSPI-CLK11: U67.6, U68.52
QSPI-CS: R5.1, R9.1, U4.1, U5.56
QSPI-CS1: R22.1, R23.1, U1.1, U8.56
QSPI-CS2: R38.1, R39.1, U13.1, U14.56
QSPI-CS3: R54.1, R55.1, U19.1, U20.56
QSPI-CS4: R70.1, R71.1, U25.1, U26.56
QSPI-CS5: R86.1, R87.1, U31.1, U32.56
QSPI-CS6: R102.1, R103.1, U37.1, U38.56
QSPI-CS7: R118.1, R119.1, U43.1, U44.56
QSPI-CS8: R134.1, R135.1, U49.1, U50.56
QSPI-CS9: R150.1, R151.1, U55.1, U56.56
QSPI-CS10: R166.1, R167.1, U61.1, U62.56
QSPI-CS11: R182.1, R183.1, U67.1, U68.56
SDIO_DAT1: J6.DAT1, U5.14
SDIO_DAT2: J6.DAT2, U5.13
SDIO_DAT3: J11.DAT1, U8.14
SDIO_DAT4: J11.DAT2, U8.13
SDIO_DAT5: J18.DAT1, U14.14
SDIO_DAT6: J18.DAT2, U14.13
SDIO_DAT7: J25.DAT1, U20.14
SDIO_DAT8: J25.DAT2, U20.13
SDIO_DAT9: J32.DAT1, U26.14
SDIO_DAT10: J32.DAT2, U26.13
SDIO_DAT11: J39.DAT1, U32.14
SDIO_DAT12: J39.DAT2, U32.13
SDIO_DAT13: J46.DAT1, U38.14
SDIO_DAT14: J46.DAT2, U38.13
SDIO_DAT15: J53.DAT1, U44.14
SDIO_DAT16: J53.DAT2, U44.13
SDIO_DAT17: J60.DAT1, U50.14
SDIO_DAT18: J60.DAT2, U50.13
SDIO_DAT19: J67.DAT1, U56.14
SDIO_DAT20: J67.DAT2, U56.13
SDIO_DAT21: J74.DAT1, U62.14
SDIO_DAT22: J74.DAT2, U62.13
SDIO_DAT23: J81.DAT1, U68.14
SDIO_DAT24: J81.DAT2, U68.13
SPI0_CIPO: J7.13, U5.6
SPI0_CIPO1: J12.13, U8.6
SPI0_CIPO2: J19.13, U14.6
SPI0_CIPO3: J26.13, U20.6
SPI0_CIPO4: J33.13, U26.6
SPI0_CIPO5: J40.13, U32.6
SPI0_CIPO6: J47.13, U38.6
SPI0_CIPO7: J54.13, U44.6
SPI0_CIPO8: J61.13, U50.6
SPI0_CIPO9: J68.13, U56.6
SPI0_CIPO10: J75.13, U62.6
SPI0_CIPO11: J82.13, U68.6
SPI0_COPI: J7.12, U5.5
SPI0_COPI1: J12.12, U8.5
SPI0_COPI2: J19.12, U14.5
SPI0_COPI3: J26.12, U20.5
SPI0_COPI4: J33.12, U26.5
SPI0_COPI5: J40.12, U32.5
SPI0_COPI6: J47.12, U38.5
SPI0_COPI7: J54.12, U44.5
SPI0_COPI8: J61.12, U50.5
SPI0_COPI9: J68.12, U56.5
SPI0_COPI10: J75.12, U62.5
SPI0_COPI11: J82.12, U68.5
SPI0_SCK: J7.11, U5.4
SPI0_SCK1: J12.11, U8.4
SPI0_SCK2: J19.11, U14.4
SPI0_SCK3: J26.11, U20.4
SPI0_SCK4: J33.11, U26.4
SPI0_SCK5: J40.11, U32.4
SPI0_SCK6: J47.11, U38.4
SPI0_SCK7: J54.11, U44.4
SPI0_SCK8: J61.11, U50.4
SPI0_SCK9: J68.11, U56.4
SPI0_SCK10: J75.11, U62.4
SPI0_SCK11: J82.11, U68.4
SPI_!CS1!/SDIO_DAT1: J11.CS/DAT3, U8.12
SPI_!CS1!/SDIO_DAT2: J18.CS/DAT3, U14.12
SPI_!CS1!/SDIO_DAT3: J6.CS/DAT3, U5.12
SPI_!CS1!/SDIO_DAT4: J25.CS/DAT3, U20.12
SPI_!CS1!/SDIO_DAT5: J32.CS/DAT3, U26.12
SPI_!CS1!/SDIO_DAT6: J39.CS/DAT3, U32.12
SPI_!CS1!/SDIO_DAT7: J46.CS/DAT3, U38.12
SPI_!CS1!/SDIO_DAT8: J53.CS/DAT3, U44.12
SPI_!CS1!/SDIO_DAT9: J60.CS/DAT3, U50.12
SPI_!CS1!/SDIO_DAT10: J67.CS/DAT3, U56.12
SPI_!CS1!/SDIO_DAT11: J74.CS/DAT3, U62.12
SPI_!CS1!/SDIO_DAT12: J81.CS/DAT3, U68.12
SPI_CIPO1/SDIO_DAT0: J6.DO/DAT0, U5.15
SPI_CIPO1/SDIO_DAT1: J11.DO/DAT0, U8.15
SPI_CIPO1/SDIO_DAT2: J18.DO/DAT0, U14.15
SPI_CIPO1/SDIO_DAT3: J25.DO/DAT0, U20.15
SPI_CIPO1/SDIO_DAT4: J32.DO/DAT0, U26.15
SPI_CIPO1/SDIO_DAT5: J39.DO/DAT0, U32.15
SPI_CIPO1/SDIO_DAT6: J46.DO/DAT0, U38.15
SPI_CIPO1/SDIO_DAT7: J53.DO/DAT0, U44.15
SPI_CIPO1/SDIO_DAT8: J60.DO/DAT0, U50.15
SPI_CIPO1/SDIO_DAT9: J67.DO/DAT0, U56.15
SPI_CIPO1/SDIO_DAT10: J74.DO/DAT0, U62.15
SPI_CIPO1/SDIO_DAT11: J81.DO/DAT0, U68.15
SPI_COPI1/SDIO_CMD: J6.DI/CMD, U5.18
SPI_COPI1/SDIO_CMD1: J11.DI/CMD, U8.18
SPI_COPI1/SDIO_CMD2: J18.DI/CMD, U14.18
SPI_COPI1/SDIO_CMD3: J25.DI/CMD, U20.18
SPI_COPI1/SDIO_CMD4: J32.DI/CMD, U26.18
SPI_COPI1/SDIO_CMD5: J39.DI/CMD, U32.18
SPI_COPI1/SDIO_CMD6: J46.DI/CMD, U38.18
SPI_COPI1/SDIO_CMD7: J53.DI/CMD, U44.18
SPI_COPI1/SDIO_CMD8: J60.DI/CMD, U50.18
SPI_COPI1/SDIO_CMD9: J67.DI/CMD, U56.18
SPI_COPI1/SDIO_CMD10: J74.DI/CMD, U62.18
SPI_COPI1/SDIO_CMD11: J81.DI/CMD, U68.18
SPI_SCK1/SDIO_CLK: J6.SCLK, U5.17
SPI_SCK1/SDIO_CLK1: J11.SCLK, U8.17
SPI_SCK1/SDIO_CLK2: J18.SCLK, U14.17
SPI_SCK1/SDIO_CLK3: J25.SCLK, U20.17
SPI_SCK1/SDIO_CLK4: J32.SCLK, U26.17
SPI_SCK1/SDIO_CLK5: J39.SCLK, U32.17
SPI_SCK1/SDIO_CLK6: J46.SCLK, U38.17
SPI_SCK1/SDIO_CLK7: J53.SCLK, U44.17
SPI_SCK1/SDIO_CLK8: J60.SCLK, U50.17
SPI_SCK1/SDIO_CLK9: J67.SCLK, U56.17
SPI_SCK1/SDIO_CLK10: J74.SCLK, U62.17
SPI_SCK1/SDIO_CLK11: J81.SCLK, U68.17
SWDCK: J1.4, TP1.P$1, U5.24
SWDCK1: J14.4, TP4.P$1, U8.24
SWDCK2: J21.4, TP7.P$1, U14.24
SWDCK3: J28.4, TP10.P$1, U20.24
SWDCK4: J35.4, TP13.P$1, U26.24
SWDCK5: J42.4, TP16.P$1, U32.24
SWDCK6: J49.4, TP19.P$1, U38.24
SWDCK7: J56.4, TP22.P$1, U44.24
SWDCK8: J63.4, TP25.P$1, U50.24
SWDCK9: J70.4, TP28.P$1, U56.24
SWDCK10: J77.4, TP31.P$1, U62.24
SWDCK11: J84.4, TP34.P$1, U68.24
SWDIO: J1.2, TP2.P$1, U5.25
SWDIO1: J14.2, TP5.P$1, U8.25
SWDIO2: J21.2, TP8.P$1, U14.25
SWDIO3: J28.2, TP11.P$1, U20.25
SWDIO4: J35.2, TP14.P$1, U26.25
SWDIO5: J42.2, TP17.P$1, U32.25
SWDIO6: J49.2, TP20.P$1, U38.25
SWDIO7: J56.2, TP23.P$1, U44.25
SWDIO8: J63.2, TP26.P$1, U50.25
SWDIO9: J70.2, TP29.P$1, U56.25
SWDIO10: J77.2, TP32.P$1, U62.25
SWDIO11: J84.2, TP35.P$1, U68.25
UART0_RX: J7.14, U5.3
UART0_RX1: J12.14, U8.3
UART0_RX2: J19.14, U14.3
UART0_RX3: J26.14, U20.3
UART0_RX4: J33.14, U26.3
UART0_RX5: J40.14, U32.3
UART0_RX6: J47.14, U38.3
UART0_RX7: J54.14, U44.3
UART0_RX8: J61.14, U50.3
UART0_RX9: J68.14, U56.3
UART0_RX10: J75.14, U62.3
UART0_RX11: J82.14, U68.3
UART0_TX: J7.15, U5.2
UART0_TX1: J12.15, U8.2
UART0_TX2: J19.15, U14.2
UART0_TX3: J26.15, U20.2
UART0_TX4: J33.15, U26.2
UART0_TX5: J40.15, U32.2
UART0_TX6: J47.15, U38.2
UART0_TX7: J54.15, U44.2
UART0_TX8: J61.15, U50.2
UART0_TX9: J68.15, U56.2
UART0_TX10: J75.15, U62.2
UART0_TX11: J82.15, U68.2
USB_F_N: R12.2, U5.46
USB_F_N1: R18.2, U8.46
USB_F_N2: R34.2, U14.46
USB_F_N3: R50.2, U20.46
USB_F_N4: R66.2, U26.46
USB_F_N5: R82.2, U32.46
USB_F_N6: R98.2, U38.46
USB_F_N7: R114.2, U44.46
USB_F_N8: R130.2, U50.46
USB_F_N9: R146.2, U56.46
USB_F_N10: R162.2, U62.46
USB_F_N11: R178.2, U68.46
USB_F_P: R13.2, U5.47
USB_F_P1: R19.2, U8.47
USB_F_P2: R35.2, U14.47
USB_F_P3: R51.2, U20.47
USB_F_P4: R67.2, U26.47
USB_F_P5: R83.2, U32.47
USB_F_P6: R99.2, U38.47
USB_F_P7: R115.2, U44.47
USB_F_P8: R131.2, U50.47
USB_F_P9: R147.2, U56.47
USB_F_P10: R163.2, U62.47
USB_F_P11: R179.2, U68.47
USB_N: J5.A7, J5.B7, R12.1
USB_N1: J10.A7, J10.B7, R18.1
USB_N2: J17.A7, J17.B7, R34.1
USB_N3: J24.A7, J24.B7, R50.1
USB_N4: J31.A7, J31.B7, R66.1
USB_N5: J38.A7, J38.B7, R82.1
USB_N6: J45.A7, J45.B7, R98.1
USB_N7: J52.A7, J52.B7, R114.1
USB_N8: J59.A7, J59.B7, R130.1
USB_N9: J66.A7, J66.B7, R146.1
USB_N10: J73.A7, J73.B7, R162.1
USB_N11: J80.A7, J80.B7, R178.1
USB_P: J5.A6, J5.B6, R13.1
USB_P1: J10.A6, J10.B6, R19.1
USB_P2: J17.A6, J17.B6, R35.1
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
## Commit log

2020-11-20 Airwire in progress
2020-11-23 airwire corrections
2020-12-01 v01 review
2020-12-02 Review Changes
    - Add "Pi Thing Plus RP2040" silk
    - Align LEDs
    - Change LED label style
    - Flip bottom silk labels
    - Add GND vias
    - Beef up power traces
2020-12-02 Move silk on LiPo connector. Add ignore. Remove backups.
2020-12-02 Run lib update on schematic. Compress schematic wires. Push production files.
2020-12-30 Change res on charger to 2k
2020-12-30 Correct product name silk
2021-01-07 Panel with 2k charge resistor
2021-01-14 Add TPs to SWD. Connect reset. v11.
2021-01-14 Panelize v11
2021-01-15 Add RP2040 Logo
2021-01-15 Update RP2040 Logo
2021-01-20 Update README.md
    Updated product image link
    Added brief product description
    Included link to RP2040 datasheet
2021-03-16 Update README.md
    Fix image link
2021-08-06 Added ARM DevSummit Logo
    Removed logos from bottom of PCB and replaced with ARM DevSummit logo.
